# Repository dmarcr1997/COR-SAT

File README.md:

# COR-SAT

COR-SAT turns natural-language mission requests into tested Python mission packages for a Raspberry Pi satellite payload. It combines AI-assisted generation, deterministic evaluation, a supervised runtime, a Python hardware SDK, a Rust HAL, camera capture, and prototype infrared communications hardware.

> Experimental project. Generated missions are limited to the capabilities and checks documented below.

## System overview

```mermaid
flowchart LR
    A[Mission request] --> B[Typed requirements]
    B --> C[Minimal generator]
    C --> D{Evaluator}
    D -->|Pass| H[Mission package]
    D -->|Fail| E[Robust generator]
    E --> D
    D -->|Both fail| F[Repair once]
    F --> D
    H --> I[Runner]
    I --> J[Python SDK]
    J --> K[Rust HAL]
    K --> L[Pi camera]

    M[IR breadboard] -. prototype .-> N[KiCad PCB]
```

Model calls return text only and never write project files. The controller validates requirements, evaluates behavior, writes the package, derives `manifest.json`, and validates the final package against the runner schema.

## Project status

| Area | Status |
| --- | --- |
| Camera mission generation | Working |
| Timed capture and heartbeats | Working |
| Shutdown handling | Working |
| Sparse Lucas-Kanade optical flow | Working |
| Mission supervision and logs | Working on Linux and Raspberry Pi OS |
| IR communications hardware | Breadboard and KiCad prototype |
| IR communications mission API | Not implemented |
| IMU and actuator support | Not implemented |

## Repository map

| Path | Purpose |
| --- | --- |
| `agents/` | Parse, generate, evaluate, repair, and package missions |
| `runner/` | Validate, launch, supervise, stop, and inspect missions |
| `sdk/` | Python client for the satellite HAL |
| `hal/` | Rust HTTP service for camera and system access |
| `missions/` | Reviewed mission packages |
| `runtime/` | Mission state, heartbeat data, and logs |
| `schematics/` | KiCad project, schematic PDF, PCB, and STEP models |
| `demo/` | Offline HTML presentation with embedded media |
| `tests/` | Unit and acceptance tests |

## Requirements

### Development and mission generation

- Git
- Python 3.11+
- [Ollama](https://ollama.com/)
- `qwen3:4b-instruct`

### Physical payload runtime

- Raspberry Pi running Linux or Raspberry Pi OS
- Rust 1.85+ and Cargo
- Raspberry Pi camera stack with `rpicam-still`
- IMX219 NoIR camera for the current HAL tuning configuration

### Optional optical flow

- OpenCV
- NumPy

Mission generation and tests can run without camera hardware. Physical mission execution and runner supervision are intended for Linux or the Raspberry Pi.

## 1. Clone and install

```bash
git clone https://github.com/dmarcr1997/COR-SAT.git
cd COR-SAT
python -m venv .venv
```

Activate the environment:

| Platform | Command |
| --- | --- |
| Linux or Raspberry Pi | `source .venv/bin/activate` |
| Windows PowerShell | `.\.venv\Scripts\Activate.ps1` |

Commands below use `python`. On Raspberry Pi OS, use `python3` if `python` is not available.

Install the SDK and generation dependencies:

```bash
python -m pip install --upgrade pip
python -m pip install -e . ollama requests
```

For missions that calculate optical flow:

```bash
python -m pip install opencv-python numpy
```

## 2. Configure Ollama

Pull the model used by the generator:

```bash
ollama pull qwen3:4b-instruct
```

Start Ollama if it is not already running:

```bash
ollama serve
```

The generator expects Ollama on its default local endpoint and uses `qwen3:4b-instruct`. The model is configured in `agents/generator.py`. There is currently no project CLI flag for changing the model or Ollama host.

## 3. Verify the software setup

```bash
python -m unittest discover -s tests -v
cargo test --manifest-path hal/Cargo.toml
```

The Python suite mocks model calls, camera hardware, time delays, and OpenCV behavior. It does not require Ollama or a connected camera. The Cargo command tests the Rust HAL.

## 4. Generate a mission

```bash
python -m agents.cli "Capture seven images at three-second intervals and send a heartbeat before every capture." --candidate demo
```

Generated files:

```text
agents/candidates/demo/
|-- manifest.json
`-- mission.py
```

Use a new candidate name for each run. Existing candidate directories are not overwritten.

### Supported request examples

```text
Capture one image.
Capture five images at two-second intervals.
Capture twenty images and calculate sparse optical flow in four groups.
Capture seven images, heartbeat before each capture, and handle shutdown signals.
```

Requests for communications, IMU, or actuator behavior are rejected before generation.

## 5. Prepare the Raspberry Pi

Install the camera module and use a current Raspberry Pi OS release. Raspberry Pi OS includes the standard `rpicam-*` tools. See the official [camera setup guide](https://www.raspberrypi.com/documentation/computers/camera_software.html).

Install Rust with [rustup](https://www.rust-lang.org/tools/install), then select an edition 2024-compatible toolchain:

```bash
curl --proto '=https' --tlsv1.2 -sSf https://sh.rustup.rs | sh
source "$HOME/.cargo/env"
rustup update stable
rustc --version
```

Rust 1.85 or newer is required.

Confirm that the camera stack can see the sensor:

```bash
rpicam-still --list-cameras
```

The current HAL uses the Raspberry Pi 5 IMX219 NoIR tuning file. Confirm it exists:

```bash
test -f /usr/share/libcamera/ipa/rpi/pisp/imx219_noir.json
```

Earlier Raspberry Pi models store tuning files under `/usr/share/libcamera/ipa/rpi/vc4/`. Update the HAL tuning path before building if you use one of those models.

Build the HAL:

```bash
cargo build --release --manifest-path hal/Cargo.toml
```

Start the HAL from the repository root:

```bash
cargo run --release --manifest-path hal/Cargo.toml
```

The service listens on `0.0.0.0:3000`. The Python SDK connects to `http://localhost:3000` by default, so the runner and HAL should run on the same Pi unless the client configuration is changed.

### Verify the HAL

```bash
curl http://localhost:3000/v1/system/health
curl http://localhost:3000/v1/system/status
curl http://localhost:3000/v1/system/capabilities
curl -X POST http://localhost:3000/v1/camera/capture
```

Camera captures are written to `hal/caps/` when the HAL is started from the repository root.

## 6. Run a mission

Run the included camera mission:

```bash
python -m runner.cli supervise periodic-camera
```

Run a generated candidate:

```bash
python -m runner.cli supervise demo --candidate
```

`supervise` monitors the process, checks heartbeats, and restarts one unexpected failure. Use `start` when supervision is not needed.

`supervise` stays in the foreground. Open a second terminal to inspect status or logs, or to stop the mission.

## Runtime controls

| Action | Command |
| --- | --- |
| Start reviewed mission | `python -m runner.cli start periodic-camera` |
| Supervise reviewed mission | `python -m runner.cli supervise periodic-camera` |
| Start candidate | `python -m runner.cli start demo --candidate` |
| Supervise candidate | `python -m runner.cli supervise demo --candidate` |
| Show status | `python -m runner.cli status demo` |
| Show logs | `python -m runner.cli logs demo --lines 100` |
| Stop mission | `python -m runner.cli stop demo` |

Runtime artifacts:

```text
runtime/<mission-name>/
|-- heartbeat.json
|-- mission.log
`-- state.json
```

Mission-generated files are stored beside the mission code:

| Mission type | Output directory |
| --- | --- |
| Reviewed | `missions/<name>/outputs/` |
| Candidate | `agents/candidates/<name>/outputs/` |

Optical-flow missions write JPEG results to that `outputs/` directory.

## Validation pipeline

Every candidate must pass:

1. Validated typed requirements
2. Python syntax checks
3. Import and file-write safety checks
4. Fake SDK execution
5. Capture, timing, heartbeat, and output checks
6. Mission-specific optical-flow checks when requested
7. Runner manifest validation

If both generated candidates fail, the highest-scoring failure is repaired once and evaluated again. A failed repair stops the pipeline without creating a package.

## Hardware

The camera payload is connected through the Rust HAL. The infrared link is a separate hardware prototype and is not yet exposed through the SDK or mission generator.

| Artifact | Link |
| --- | --- |
| KiCad project | [`sat_ir_link.kicad_pro`](schematics/sat_ir_link/sat_ir_link.kicad_pro) |
| PCB layout | [`sat_ir_link.kicad_pcb`](schematics/sat_ir_link/sat_ir_link.kicad_pcb) |
| Schematic | [`sat_ir_link.kicad_sch`](schematics/sat_ir_link/sat_ir_link.kicad_sch) |
| Schematic PDF | [`sat_ir_link.pdf`](schematics/sat_ir_link.pdf) |
| Board STEP model | [`v23d-print-board.step`](schematics/sat_ir_link/v23d-print-board.step) |

## Presentation demo

Open [`demo/index.html`](demo/index.html) in a browser. The presentation works offline and includes keyboard navigation, speaker notes, the software demonstration, and project hardware images.

| Key | Action |
| --- | --- |
| Left or Right arrow | Change slide |
| `N` | Toggle speaker notes |
| `F` | Toggle fullscreen |

## Troubleshooting

| Problem | Check |
| --- | --- |
| Ollama connection fails | Run `ollama serve` and confirm the model is pulled |
| Candidate already exists | Choose a new value for `--candidate` |
| HAL reports an unhealthy camera | Run `rpicam-still --list-cameras` |
| Camera capture fails | Confirm `rpicam-still` and the IMX219 NoIR tuning file are installed |
| Mission cannot reach HAL | Confirm the HAL is running on port `3000` on the same host |
| Supervision or stop fails on Windows | Run the mission runtime on Linux or Raspberry Pi OS |
| Optical-flow mission fails at runtime | Install `opencv-python` and `numpy` in the mission environment |

## License

[MIT](LICENSE)

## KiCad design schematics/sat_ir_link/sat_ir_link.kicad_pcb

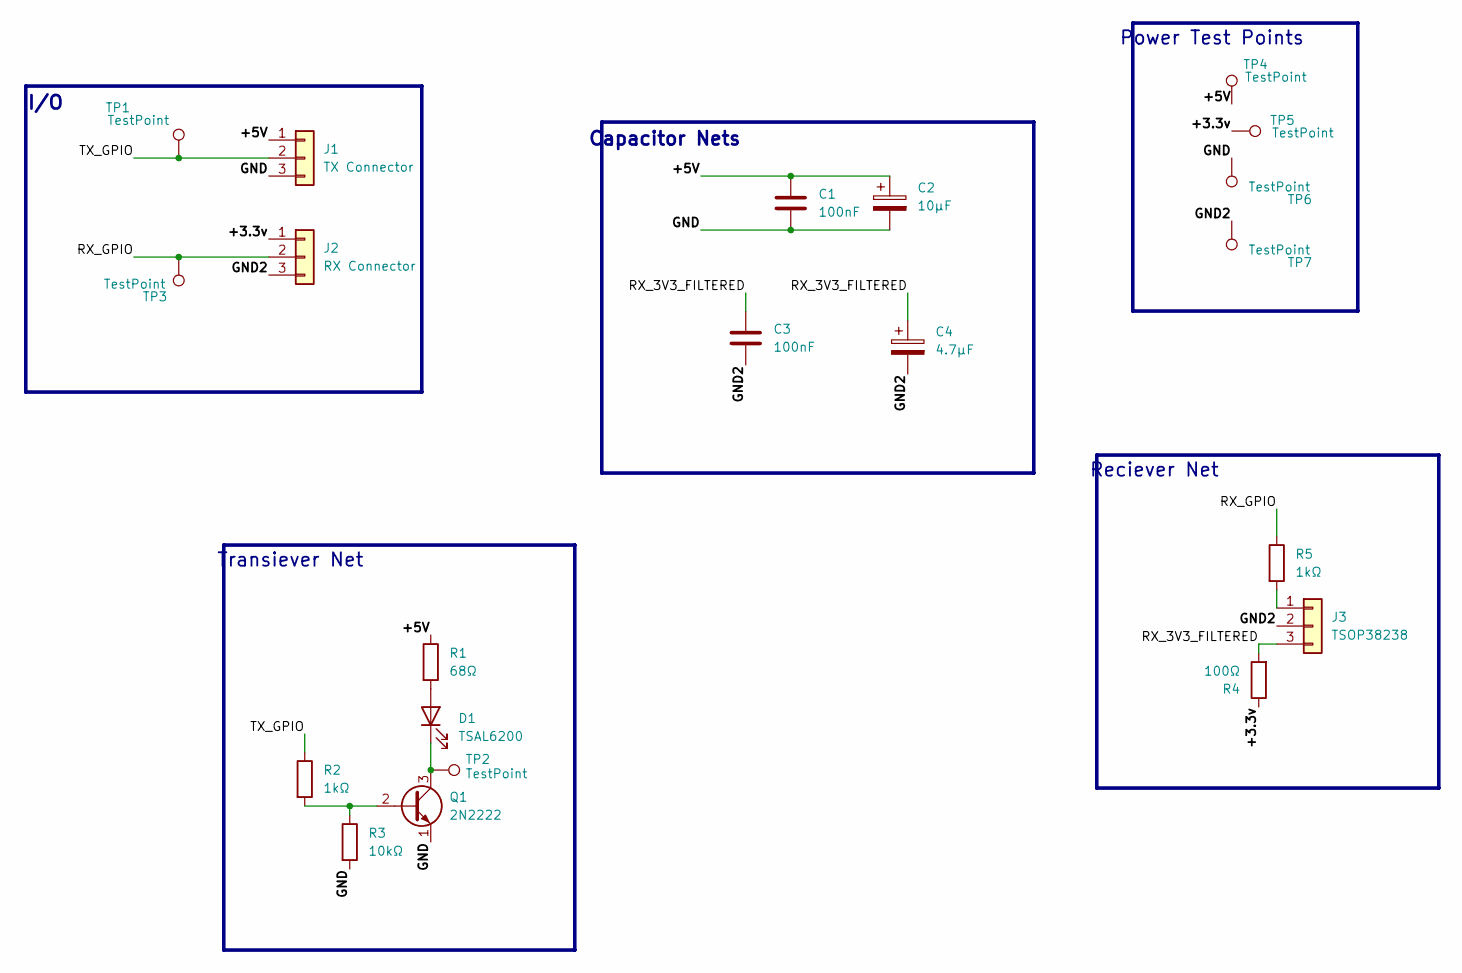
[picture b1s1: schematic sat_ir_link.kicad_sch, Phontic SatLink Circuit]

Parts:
C1, C3: 100nF; C_Disc_D5.0mm_W2.5mm_P5.00mm
C2: 10µF; CP_Radial_D5.0mm_P2.00mm
C4: 4.7µF; CP_Radial_D5.0mm_P2.00mm
D1: TSAL6200; LED_D5.0mm
J1: TX Connector; FanPinHeader_1x03_P2.54mm_Vertical
J2: RX Connector; FanPinHeader_1x03_P2.54mm_Vertical
J3: TSOP38238; FanPinHeader_1x03_P2.54mm_Vertical
Q1: 2N2222; TO-92_Inline
R1: 68Ω; R_Axial_DIN0207_L6.3mm_D2.5mm_P10.16mm_Horizontal
R2, R5: 1kΩ; R_Axial_DIN0207_L6.3mm_D2.5mm_P10.16mm_Horizontal
R3: 10kΩ; R_Axial_DIN0207_L6.3mm_D2.5mm_P10.16mm_Horizontal
R4: 100Ω; R_Axial_DIN0207_L6.3mm_D2.5mm_P10.16mm_Horizontal
TP1, TP2, TP3, TP4, TP5, TP6, TP7: TestPoint; TestPoint_THTPad_D4.0mm_Drill2.0mm

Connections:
/+3.3v: J2.1, R4.1, TP5.1 (1_1)
/+5V: C1.1, C2.1, J1.1, R1.1, TP4.1 (1_1)
/GND: C1.2, C2.2, J1.3, Q1.1 (E), R3.2, TP6.1 (1_1)
/GND2: C3.2, C4.2, J2.3, J3.2, TP7.1 (1_1)
/RX_3V3_FILTERED: C3.1, C4.1, J3.3, R4.2
/RX_GPIO: J2.2, R5.1, TP3.1 (1_1)
/TX_GPIO: J1.2, R2.1, TP1.1 (1_1)
unnamed: D1.2 (A), R1.2
unnamed: D1.1 (K), Q1.3 (C), TP2.1 (1_1)
unnamed: J3.1, R5.2
unnamed: Q1.2 (B), R2.2, R3.1

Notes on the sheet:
I/O
Power Test Points
Transiever Net
Reciever Net
Capacitor Nets

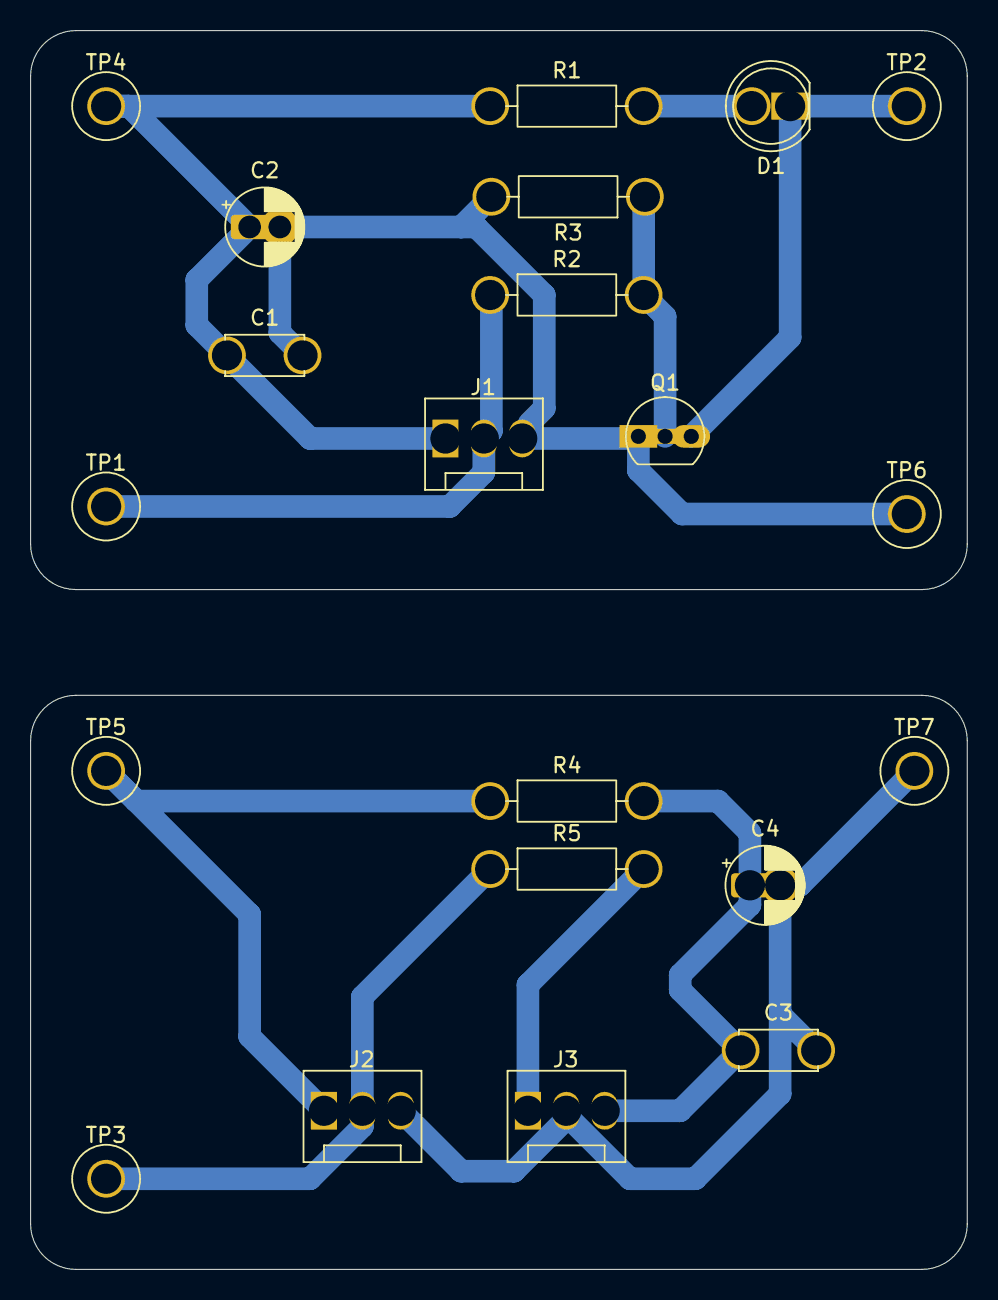
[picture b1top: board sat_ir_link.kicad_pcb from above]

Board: 2 copper layers, 62.0 x 82.0 mm, 21 parts (0 on the bottom side), 11 nets.
